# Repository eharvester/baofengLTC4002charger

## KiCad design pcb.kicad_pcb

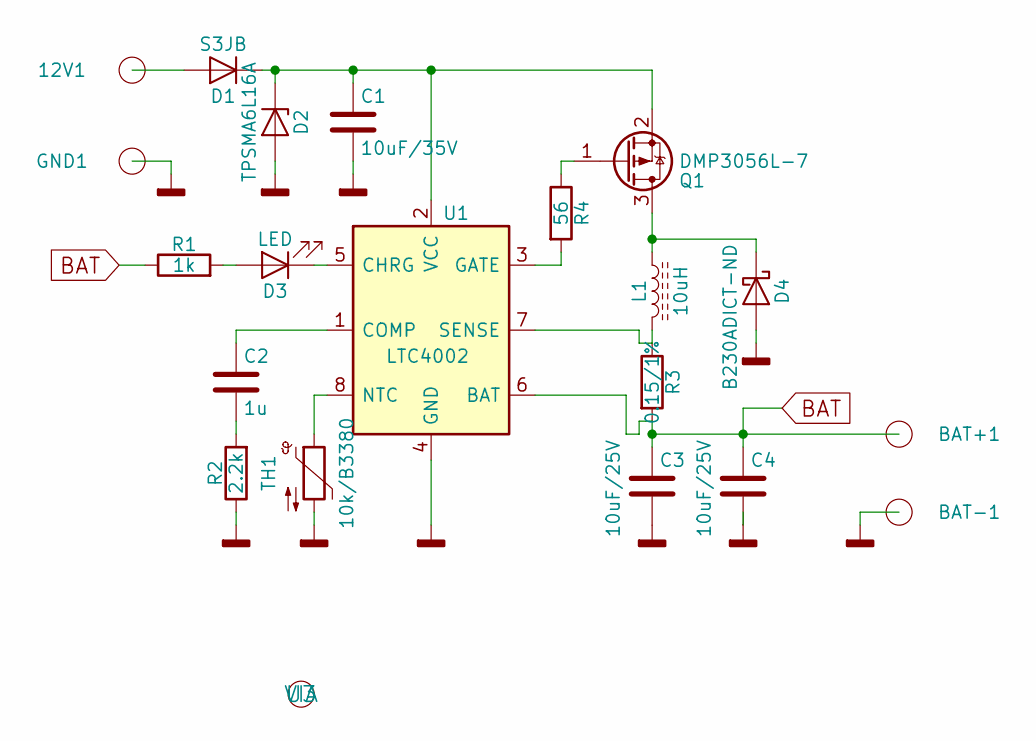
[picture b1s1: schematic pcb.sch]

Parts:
12V1: TEST_1P; VIA-1.2-2.5MM
BAT+1: TEST_1P; TerminalPad3x5
BAT-1: TEST_1P; TerminalPad3x5
C1: 10uF/35V; C_1206
C2: 1u; C_0603
C3, C4: 10uF/25V; C_0805
D1: S3JB; D_SMB
D2: TPSMA6L16A; D_SMA
D3: LED; LED_D3.0mm_FlatTop
D4: B230ADICT-ND; D_SMB
GND1: TEST_1P; VIA-1.2-2.5MM
L1: 10uH; L_1210
Q1: DMP3056L-7; SOT-23
R1: 1k; R_0603
R2: 2.2k; R_0603
R3: 0.15/1%; R_0603
R4: 56; R_0603
TH1: 10k/B3380; C_Disc_D3.0mm_W1.6mm_P2.50mm
U1: LTC4002; SOIC-8_3.9x4.9mm_Pitch1.27mm
U3: VIA; VIA-0.6MM-1.6MM

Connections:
BAT: BAT+1.1, C3.1, C4.1, R1.1, R3.2, U1.6 (BAT)
GNDD: BAT-1.1, C1.2, C3.2, C4.2, D2.2 (A), D4.2 (A), GND1.1, R2.1, TH1.2, U1.4 (GND)
unnamed: 12V1.1, D1.2 (A)
unnamed: C1.1, D1.1 (K), D2.1 (K), Q1.2 (S), U1.2 (VCC)
unnamed: C2.1, U1.1 (COMP)
unnamed: C2.2, R2.2
unnamed: D3.1 (K), U1.5 (CHRG)
unnamed: D3.2 (A), R1.2
unnamed: D4.1 (K), L1.1, Q1.3 (D)
unnamed: L1.2, R3.1, U1.7 (SENSE)
unnamed: Q1.1 (G), R4.1
unnamed: R4.2, U1.3 (GATE)
unnamed: TH1.1, U1.8 (NTC)

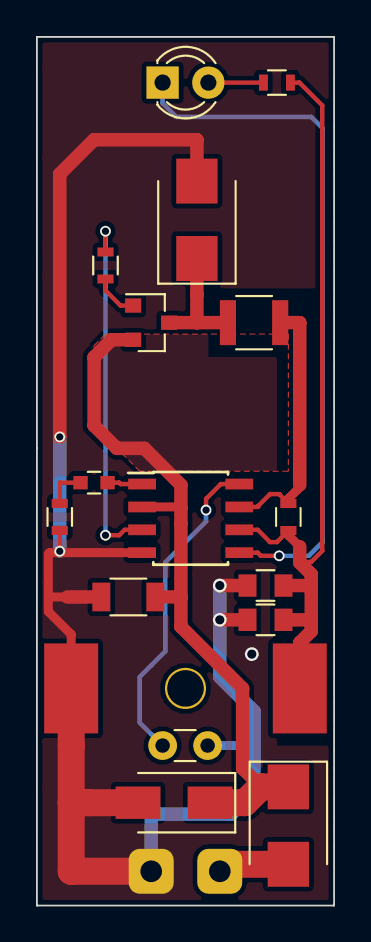
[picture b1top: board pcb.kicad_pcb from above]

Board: 2 copper layers, 16.5 x 48.3 mm, 21 parts (0 on the bottom side), 13 nets.
